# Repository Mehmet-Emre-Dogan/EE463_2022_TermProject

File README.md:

# EE463 2022 Term Project
2 kW Smart DC motor drive.

# Circuit Diagrams

## Main Block Diagram

## Main Buck Converter

## Low Power Adapter
### Schematic
<div align="center"> 

</div>

### PCB
<div align="center"> 

#### Top

#### Bottom

</div>

# Device
<div align="center"> 

## Top

## Side

## In

## Line to Neutral

## In [Wide Angle]

</div>

# Analysis
## Power
### Rated Voltage [Loaded]
<div align="center">

 </div>

### Rated Power [Loaded]
<div align="center">

 </div>

## Waveforms

### Unloaded @v 25 % Duty
<div align="center">

 </div>

## Thermals

### IGBT
<div align="center">

 </div>

### 3 Phase Diode Rectifier

<div align="center">

</div>

# Miscellaneous Demos
 ## Webserver Demo
 Webdemo could be seen via following the link below:

  https://medogan.com/test_server_demo/463_esp_webdemo.html
## IP Scanning

## Controller

# Demo Videos

 ## Motor Lab Demo
 https://www.youtube.com/watch?v=8uU4kF-YDas

 ## Motor Lab Demo [ WebGui]
 https://www.youtube.com/watch?v=bq63kfShjrk

 ## ESP Soft Starting Demo
 https://www.youtube.com/watch?v=6NDupYknA6s

 ## Optocoupler Demo
https://www.youtube.com/watch?v=Q2luOk-gndQ

 ## Testing IRFP460 N Channel MOSFET
  https://www.youtube.com/watch?v=HJyMbZKjLFo
  
 IRFP460 was not used in the project because it is not supplied by the University and its is expensive and we've left only one. [We had 2 but we burned one of them.]
 IXGH24N60C4D1 N Channel IGBT was used due to it is supplied by the University .

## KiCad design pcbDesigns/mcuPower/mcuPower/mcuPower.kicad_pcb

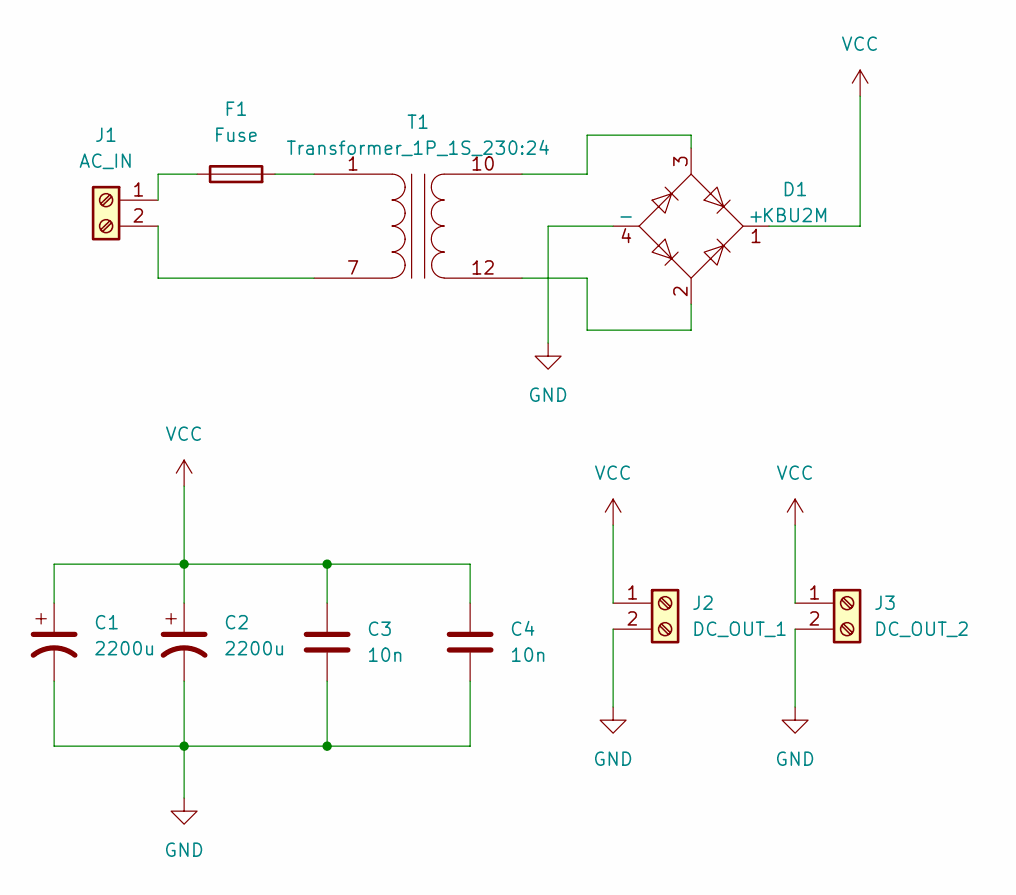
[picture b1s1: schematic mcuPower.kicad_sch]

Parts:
C1, C2: 2200u; CP_Radial_D16.0mm_P7.50mm
C3, C4: 10n; C_Disc_D5.1mm_W3.2mm_P5.00mm
D1: KBU2M; Diode_Bridge_32.0x5.6x17.0mm_P10.0mm_P7.5mm
F1: Fuse; Fuseholder_Cylinder-5x20mm_Schurter_0031_8201_Horizontal_Op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
J1: AC_IN; TerminalBlock_MetzConnect_Type175_RT02702HBLC_1x02_P7.50mm_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
J2: DC_OUT_1; TerminalBlock_MetzConnect_Type101_RT01602HBWC_1x02_P5.08mm_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
J3: DC_OUT_2; TerminalBlock_MetzConnect_Type101_RT01602HBWC_1x02_P5.08mm_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
T1: Transformer_1P_1S_230:24; Transformer_CHK_EI54-16VA_1xSec

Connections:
GND: C1.2, C2.2, C3.2, C4.2, D1.4 (-), J2.2, J3.2
unnamed: D1.2, T1.12 (SA)
unnamed: D1.3, T1.10 (SB)
unnamed: F1.1, J1.1
unnamed: F1.2, T1.1 (AA)
unnamed: J1.2, T1.7 (AB)
VCC: C1.1, C2.1, C3.1, C4.1, D1.1 (+), J2.1, J3.1

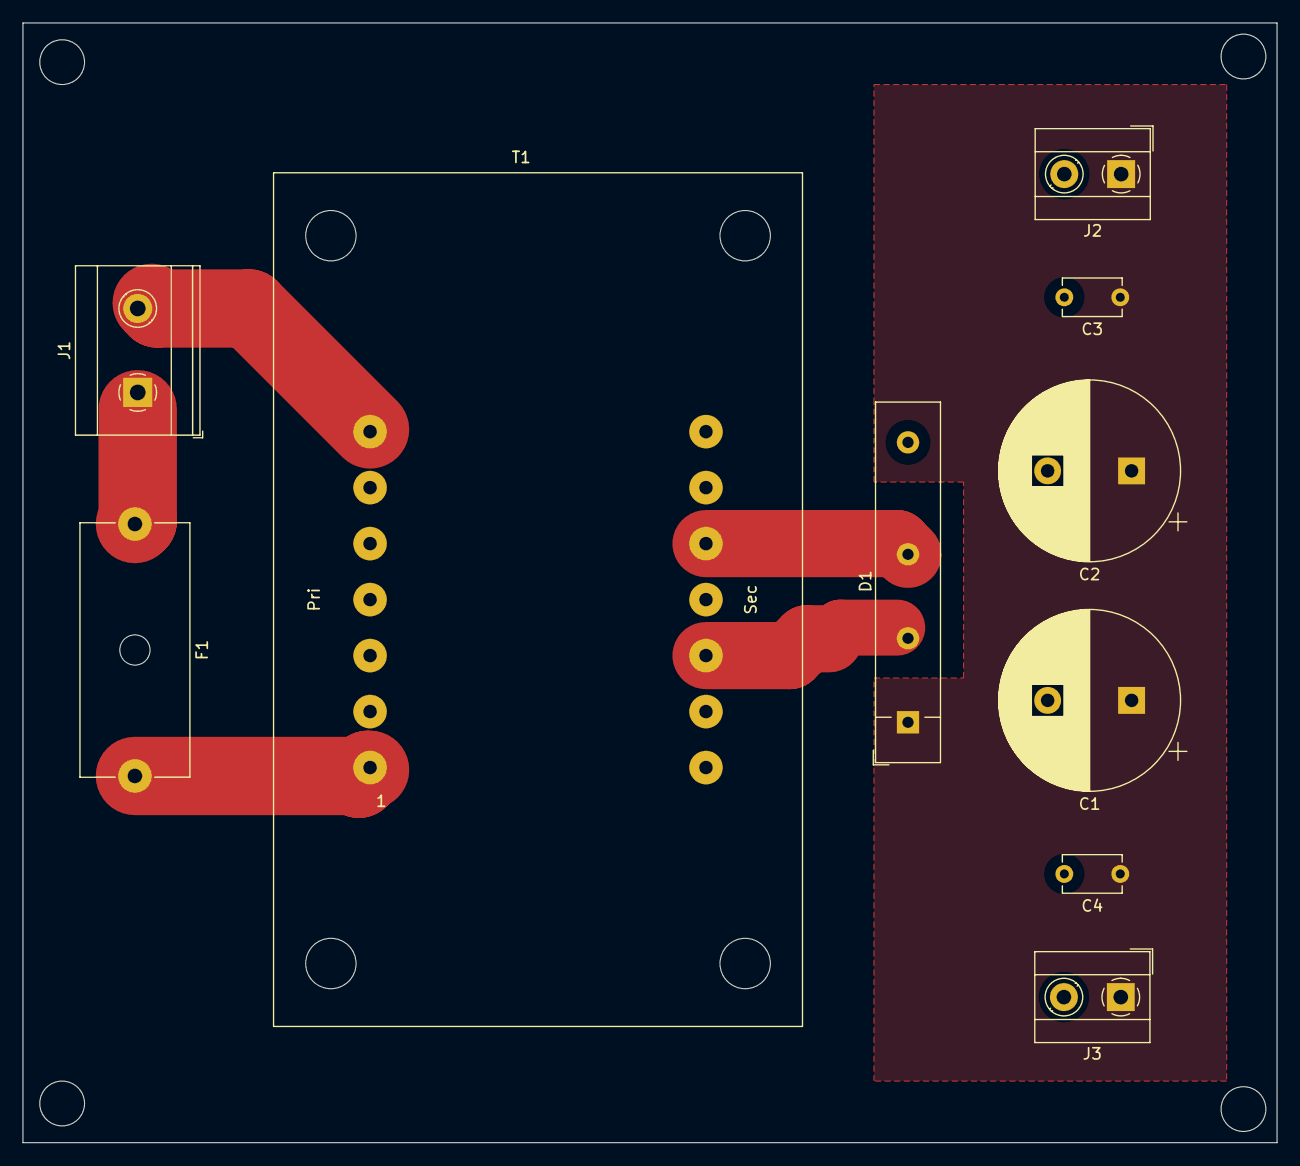
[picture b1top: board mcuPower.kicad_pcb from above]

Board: 2 copper layers, 112.0 x 100.0 mm, 10 parts (0 on the bottom side), 7 nets.

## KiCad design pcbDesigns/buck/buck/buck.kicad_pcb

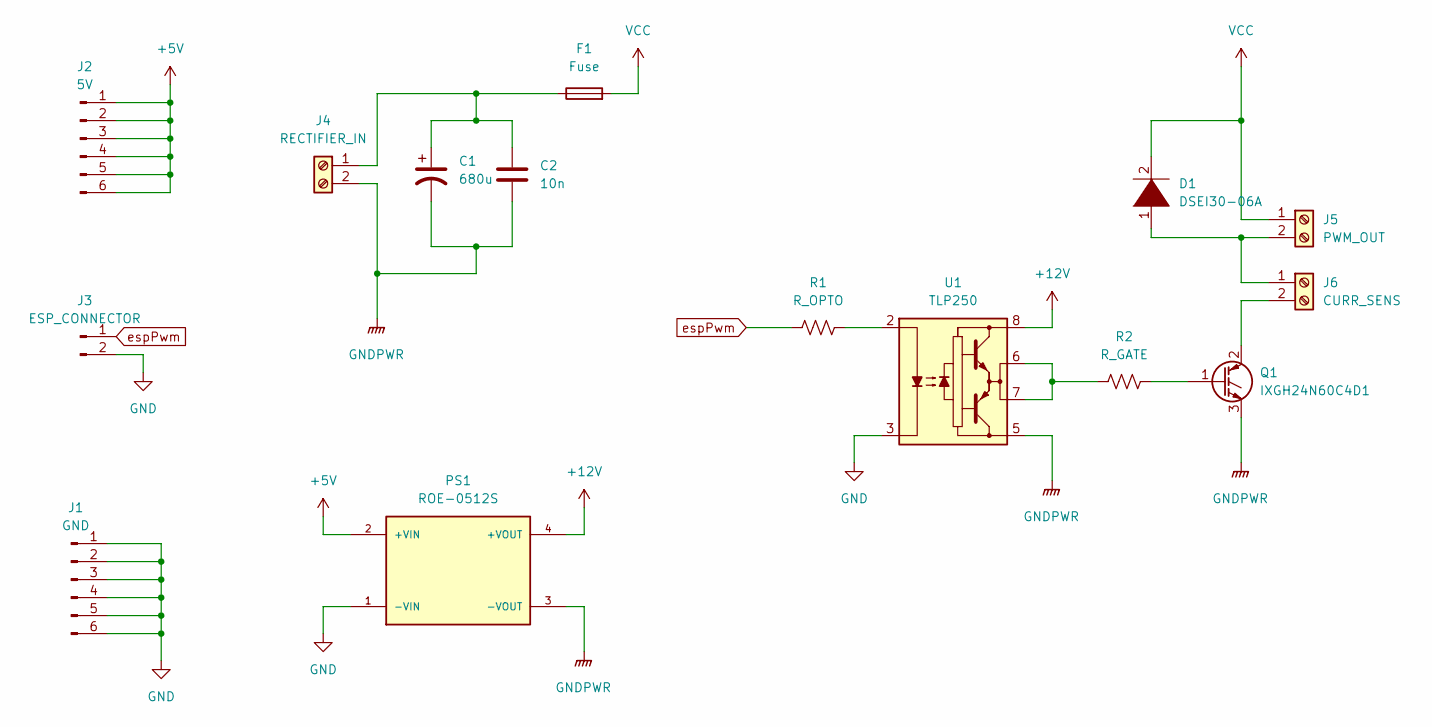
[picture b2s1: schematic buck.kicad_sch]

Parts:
C1: 680u; CP_Radial_D35.0mm_P10.00mm_SnapIn
C2: 10n; C_Disc_D5.1mm_W3.2mm_P5.00mm
D1: DSEI30-06A; TO-247-2_Vertical
F1: Fuse; Fuseholder_Cylinder-5x20mm_Schurter_0031_8201_Horizontal_Op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
J1: GND; PinHeader_1x06_P2.54mm_Vertical
J2: 5V; PinHeader_1x06_P2.54mm_Vertical
J3: ESP_CONNECTOR; PinHeader_1x02_P2.54mm_Vertical
J4: RECTIFIER_IN; TerminalBlock_MetzConnect_Type175_RT02702HBLC_1x02_P7.50mm_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
J5: PWM_OUT; TerminalBlock_MetzConnect_Type175_RT02702HBLC_1x02_P7.50mm_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
J6: CURR_SENS; TerminalBlock_MetzConnect_Type175_RT02702HBLC_1x02_P7.50mm_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
PS1: ROE-0512S; roe0512; PARTREV 5
Q1: IXGH24N60C4D1; TO-247-3_Vertical
R1: R_OPTO; R_Axial_DIN0204_L3.6mm_D1.6mm_P7.62mm_Horizontal
R2: R_GATE; R_Axial_DIN0204_L3.6mm_D1.6mm_P7.62mm_Horizontal
U1: TLP250; DIP-8_W7.62mm

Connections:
+5V: J2.1, J2.2, J2.3, J2.4, J2.5, J2.6, PS1.2 (+VIN)
+12V: PS1.4 (+VOUT), U1.8 (VCC)
GND: J1.1, J1.2, J1.3, J1.4, J1.5, J1.6, J3.2, PS1.1 (-VIN), U1.3 (C)
GNDPWR: C1.2, C2.2, J4.2, PS1.3 (-VOUT), Q1.3 (E), U1.5 (VEE)
unnamed: C1.1, C2.1, F1.1, J4.1
unnamed: D1.1 (K), J5.2, J6.1
unnamed: J6.2, Q1.2 (C)
unnamed: Q1.1 (G), R2.2
unnamed: R1.2, U1.2 (A)
unnamed: R2.1, U1.6 (VO), U1.7 (VO)
VCC: D1.2 (A), F1.2, J5.1
espPwm: J3.1, R1.1

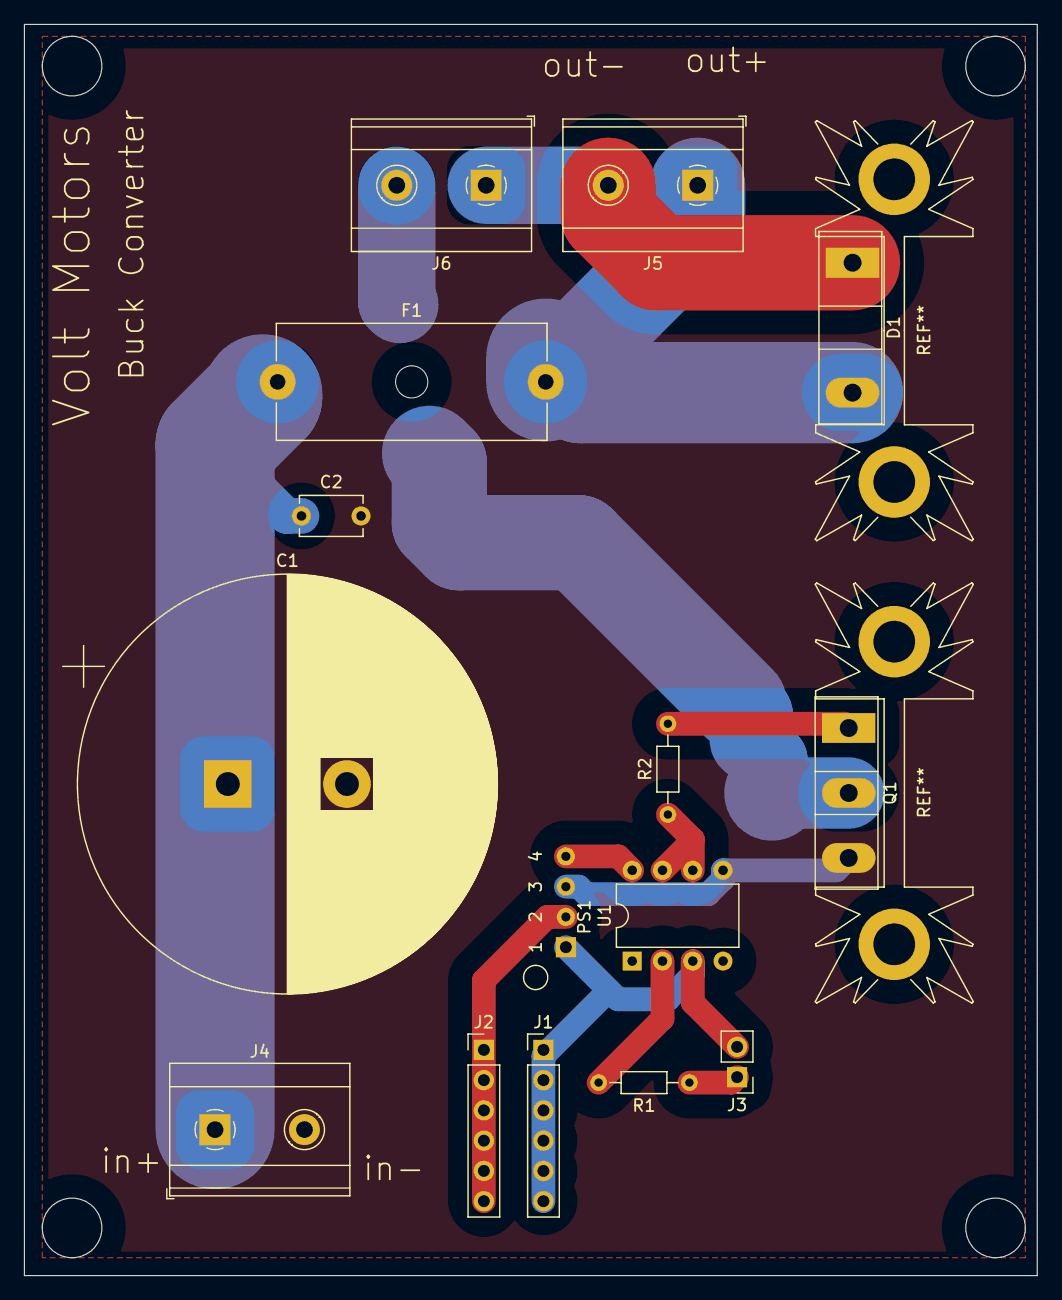
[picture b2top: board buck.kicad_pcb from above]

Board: 2 copper layers, 85.0 x 105.0 mm, 15 parts (0 on the bottom side), 12 nets.

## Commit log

2022-11-22 calculated rated voltage and currents
2022-11-26 added itemlist
2022-11-26 add missing tickboxes to list
2022-11-26 add some datasheets
2022-11-26 rectifier simulation done
2022-11-28 create a html webpage
    to later use with esp8266 [the pwm generator]
2022-11-28 improve mobile user's ergonomics
    put the slider to below the labels to prevent user's hand from blocking the display
2022-12-02 tested ESP's pwm
2022-12-02 working on advanced gate driver
2022-12-02 experimenting with famous yellow toy moyor
2022-12-02 add png versions of bmp images +
    add a current sensor's and some other datasheets
2022-12-02 simulated additional 1 phi low voltage rectifier
2022-12-02 new feature designs
    - single power supply
    - h bridge
    - dynamic braking
2022-12-03 tidy up file structure
2022-12-03 add pdf of calculations
2022-12-07 rectifier simulation done with loaded outputs
2022-12-07 simulation with pwm [mosfet not selected, default used]
2022-12-09 simulated with real diodes and mosfets and
    took screenshots for the report
2022-12-09 add transformer experiment
2022-12-09 fix image paths and readme filename
2022-12-10 Finished Complete Simulation Report as PDF
    First version of the Report
2022-12-10 Delete Volt Motors-Project Complete Simulation Report.pdf
    The report will be moved in the report folder.
2022-12-10 Finished Complete Simulation Report as PDF
    First version of the report.
2022-12-10 Finished Complete Simulation Report as Word
    First version of the report
2022-12-10 Simulation v2
    Current measurement block is added to armature winding.
2022-12-11 Update wishlist.md
    add new compnets, change fan cage with correct dimensions
2022-12-11 Update wishlist.md
    - add new elemens
2022-12-11 fix typo
2022-12-11 Update wishlist.md
    we have jumpers
2022-12-11 add new datasheets
2022-12-11 simulated with 230:24 transformer
    - filtering capacitance doubled (2*2200uF)
    - now using line line instad of line-neutral
2022-12-11 Update wishlist.md
    - ripple with 2200u seemed more to me, so decided to use 2*2200u
    - due to seperation of the fan and control transformers, we need 2 more
2022-12-11 Feedback Presentation of Volt Motors
    Feedback Presentation is completed.
2022-12-11 Thermal Calculations Added
    Thermal calculations were added.
2022-12-11 Newer Version
    Updated datasheet is found.
2022-12-11 Version 2
    Another version of the mosfet datasheet is found
2022-12-11 Analytical and thermal calculations added
    Analytical and thermal calculations were added.
2022-12-17 working on esp code
2022-12-18 move files
2022-12-18 working on webpages
2022-12-18 change ip addr
2022-12-18 hard coded serial monitor link to the button
2022-12-18 added buck pcb schematic
2022-12-18 designed pcb for the buck
2022-12-18 add pics
2022-12-19 revised buck pcb
    revision
2022-12-19 more revision
2022-12-19 add images
2022-12-19 revision: buck pcb design
    increase clearance
2022-12-21 Update README.md
    add some links for esp demo
2022-12-27 Update README.md
    add project link
2022-12-31 designed pcb for the mcu power
2022-12-31 bugfix
    fix wron connecter direction
2022-12-31 add pcb pics
2022-12-31 close file
2023-01-01 add some pics to readme + add ip scanner app
2023-01-08 add demo pictures and videos
2023-01-20 add the deprecated H bridge design
2023-01-22 add final report template
2023-01-22 Simulation with Motor Model
2023-01-22 add resistor and correct capacitor values
2023-01-22 add main block diagram
2023-01-22 update block diags
2023-01-22 update calculations
2023-01-22 design decisions report checkpoint
2023-01-22 done the design details
2023-01-22 Update designDecisions.docx
    add cooling and display subsytems
2023-01-22 Update designDecisions.docx
    add references
2023-01-23 Complete System with 2kW Output Power
2023-01-23 Complete System at Rated Voltage
2023-01-23 Complete System with 2kW Output Power
    Fundamental frequencies of mean block are corrected
2023-01-23 Complete System at Rated Voltage
    Fundamental frequencies of mean blocks are corrected
2023-01-23 Complete System with 2kW Output Power
    Output capacitor is removed due to its ideal characteristic in the simulation and input tork is adjusted
2023-01-23 Complete System at Rated Voltage
    Output capacitor is removed due to its ideal characteristic in the simulation and input tork is adjusted
2023-01-23 Transformer_Simulation
2023-01-23 Transformer_Simulation
    Input voltage is corrected
2023-01-24 Create thernals.docx
    calculated lossess
2023-01-24 Cost Table added
    A cost table with all used components is added.
2023-01-24 Complete System with 2kW Output Power
    Waveform measurements are added for armature current and output voltage
2023-01-24 Complete System at Rated Voltage
    Waveform measurements are added for armature current and output voltage. Tork input of motor model is updated.
2023-01-24 Final Report Finished
